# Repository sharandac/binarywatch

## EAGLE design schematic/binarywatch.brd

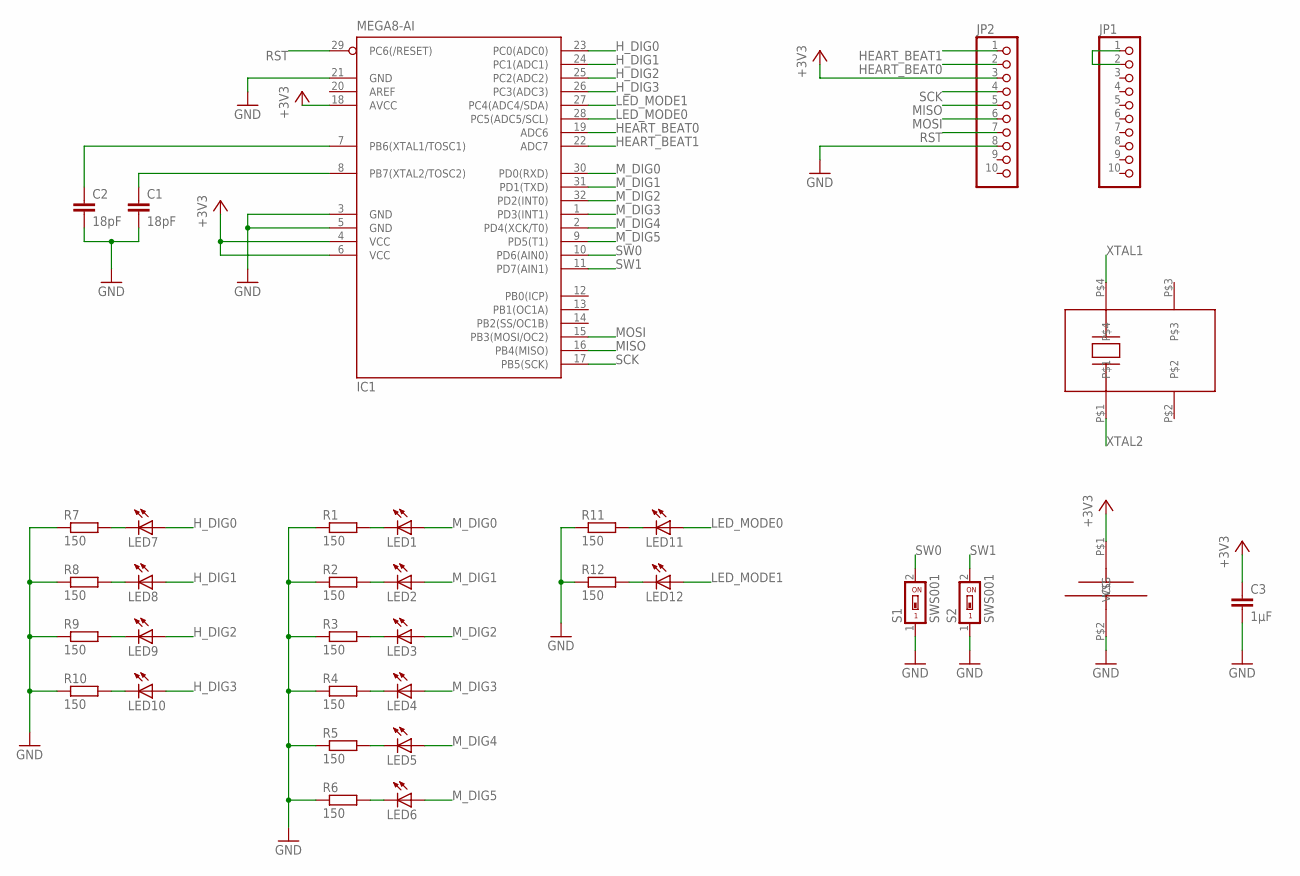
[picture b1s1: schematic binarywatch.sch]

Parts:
C1, C2: 18pF; C0805
C3: 1µF; C0805
IC1: MEGA8-AI; TQFP32-08
JP1, JP2: PINHD-1X10; 1X10
K1: LZH20-1
LED1, LED2, LED3, LED4, LED5, LED6, LED7, LED8, LED9, LED10, LED11, LED12: LEDCHIPLED_0805; CHIPLED_0805
R1, R2, R3, R4, R5, R6, R7, R8, R9, R10, R11, R12: 150; R0805
S1, S2: SWS001; SMS-001
U$1: 32768KHZ

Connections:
+3V3: C3.1, IC1.4 (VCC), IC1.6 (VCC), IC1.18 (AVCC), JP2.3, K1.P$1 (VCC)
GND: C1.2, C2.2, C3.2, IC1.3 (GND), IC1.5 (GND), IC1.21 (GND), JP2.8, K1.P$2 (VSS), R1.1, R2.1, R3.1, R4.1, R5.1, R6.1, R7.1, R8.1, R9.1, R10.1, R11.1, R12.1, S1.1, S2.1
HEART_BEAT0: IC1.19 (ADC6), JP2.2
HEART_BEAT1: IC1.22 (ADC7), JP2.1
H_DIG0: IC1.23 (PC0(ADC0)), LED7.A
H_DIG1: IC1.24 (PC1(ADC1)), LED8.A
H_DIG2: IC1.25 (PC2(ADC2)), LED9.A
H_DIG3: IC1.26 (PC3(ADC3)), LED10.A
LED_MODE0: IC1.28 (PC5(ADC5/SCL)), LED11.A
LED_MODE1: IC1.27 (PC4(ADC4/SDA)), LED12.A
MISO: IC1.16 (PB4(MISO)), JP2.5
MOSI: IC1.15 (PB3(MOSI/OC2)), JP2.6
M_DIG0: IC1.30 (PD0(RXD)), LED1.A
M_DIG1: IC1.31 (PD1(TXD)), LED2.A
M_DIG2: IC1.32 (PD2(INT0)), LED3.A
M_DIG3: IC1.1 (PD3(INT1)), LED4.A
M_DIG4: IC1.2 (PD4(XCK/T0)), LED5.A
M_DIG5: IC1.9 (PD5(T1)), LED6.A
unnamed: LED7.C, R7.2
unnamed: LED8.C, R8.2
unnamed: LED9.C, R9.2
unnamed: LED10.C, R10.2
unnamed: LED1.C, R1.2
unnamed: LED2.C, R2.2
unnamed: LED3.C, R3.2
unnamed: LED4.C, R4.2
unnamed: LED11.C, R11.2
unnamed: LED12.C, R12.2
unnamed: LED6.C, R6.2
unnamed: LED5.C, R5.2
unnamed: JP1.1, JP1.2
RST: IC1.29 (PC6(/RESET)), JP2.7
SCK: IC1.17 (PB5(SCK)), JP2.4
SW0: IC1.10 (PD6(AIN0)), S1.2
SW1: IC1.11 (PD7(AIN1)), S2.2
XTAL1: C2.1, IC1.7 (PB6(XTAL1/TOSC1)), U$1.P$4
XTAL2: C1.1, IC1.8 (PB7(XTAL2/TOSC2)), U$1.P$1

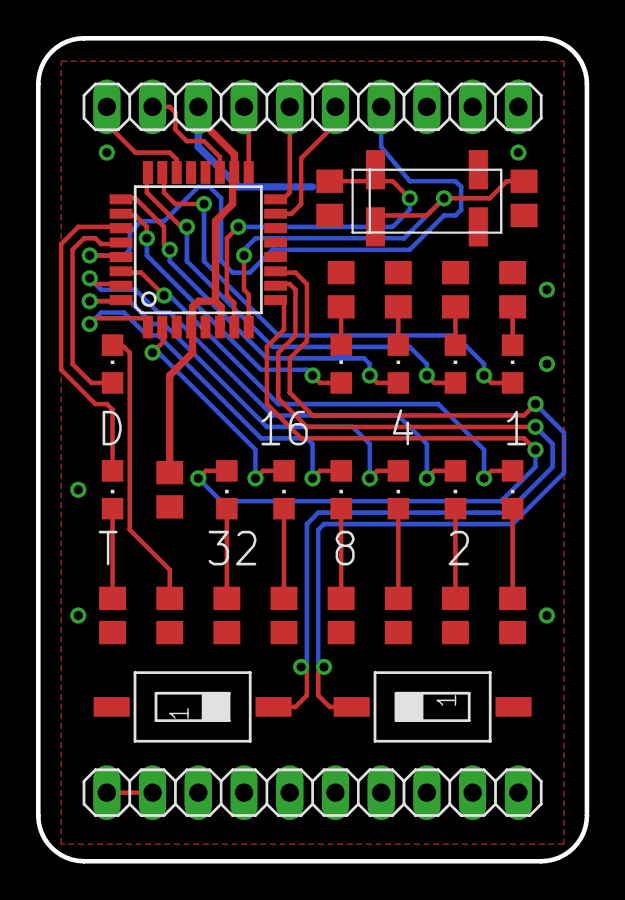
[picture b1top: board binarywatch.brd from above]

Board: 2 copper layers, 30.5 x 45.7 mm, 34 parts (1 on the bottom side), 37 nets.

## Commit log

2019-07-30 first release
